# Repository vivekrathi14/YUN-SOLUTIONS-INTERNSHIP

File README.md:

# SMART MANAGEMENT OF BINS

**Project Name** - Smart Management of Bins

**Area** - Embedded Systems, IoT

**Technolgies** - In Application Programming (IAP), Watchdog Timer (WDT), Flash Over Through Air (FOTA), GSM-2G Communication, GNSS, TCP, HTTP, FTP, I2C, Concurrency, UART, Serial Communication, Antenna Chip Design, GPIOs, ARM Cortex M0, M0516LDN, Arduino Nano

**Hardware** - ARM Cortex M0 M0516LDN

**Programming** - Embedded C

**Description** -

1. Measured the environmental quatities using sensors (Ultrasonic, IR, keypad, GSM) user input.
2. Abstracted the the senor data and sent it to server (cloud) for data handling and analysis.
3. Created to keep track of goods/objects loaded and unloaded form dockyard (or any environmental settings). 
4. Deployed for the client to keep track of packed and unpacked medicince pouches/bags in his inventory.
5. Use advanced features lik In Application Programming & Flash Over Throught Air to boot the device with updated new firmware remotely.

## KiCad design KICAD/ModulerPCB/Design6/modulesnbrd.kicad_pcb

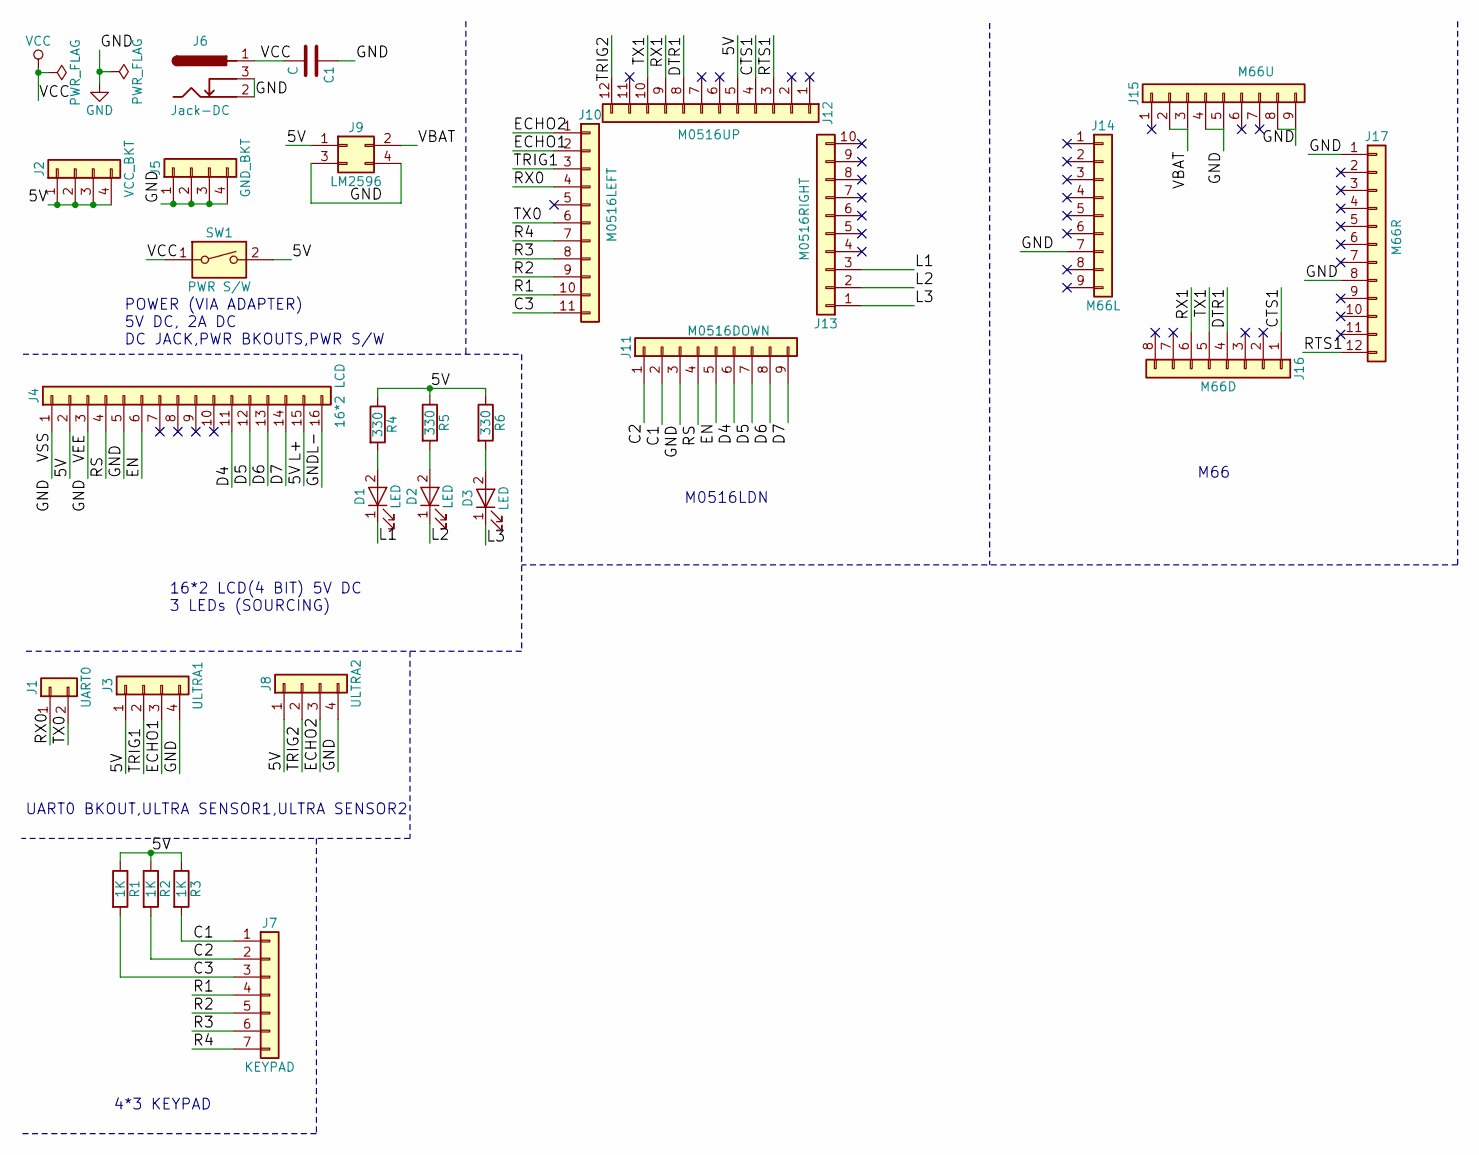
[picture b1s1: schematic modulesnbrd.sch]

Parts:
C1: C; C_Disc_D3.4mm_W2.1mm_P2.50mm
D1, D2, D3: LED; LED_D5.0mm
J1: UART0; Pin_Header_Straight_1x02_Pitch2.54mm
J2: VCC_BKT; Pin_Header_Straight_1x04_Pitch2.54mm
J3: ULTRA1; Pin_Header_Straight_1x04_Pitch2.54mm
J4: 16*2 LCD; Pin_Header_Straight_1x16_Pitch2.54mm
J5: GND_BKT; Pin_Header_Straight_1x04_Pitch2.54mm
J6: Jack-DC; Barrel_Jack_CUI_PJ-102AH
J7: KEYPAD; Pin_Header_Straight_1x07_Pitch2.54mm
J8: ULTRA2; Pin_Header_Straight_1x04_Pitch2.54mm
J9: LM2596
J10: M0516LEFT; Pin_Header_Straight_1x11_Pitch2.54mm
J11: M0516DOWN; Pin_Header_Straight_1x09_Pitch2.54mm
J12: M0516UP; Pin_Header_Straight_1x12_Pitch2.54mm
J13: M0516RIGHT; Pin_Header_Straight_1x10_Pitch2.54mm
J14: M66L; Pin_Header_Straight_1x09_Pitch2.54mm
J15: M66U; Pin_Header_Straight_1x09_Pitch2.54mm
J16: M66D; Pin_Header_Straight_1x08_Pitch2.54mm
J17: M66R; Pin_Header_Straight_1x12_Pitch2.54mm
R1, R2, R3: 1K; R_Axial_DIN0204_L3.6mm_D1.6mm_P5.08mm_Horizontal
R4, R5, R6: 330; R_Axial_DIN0204_L3.6mm_D1.6mm_P5.08mm_Horizontal
SW1: PWR S/W; SW_DIP_x1_W7.62mm_Slide

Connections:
/5V: J2.1, J2.2, J2.3, J2.4, J3.1, J4.2, J4.15, J8.1, J9.1, J12.5, R1.1, R2.1, R3.1, R4.1, R5.1, R6.1, SW1.2
/C1: J7.1, J11.2, R3.2
/C2: J7.2, J11.1, R2.2
/C3: J7.3, J10.11, R1.2
/CTS1: J12.4, J16.1
/D4: J4.11, J11.6
/D5: J4.12, J11.7
/D6: J4.13, J11.8
/D7: J4.14, J11.9
/DTR1: J12.8, J16.4
/ECHO1: J3.3, J10.2
/ECHO2: J8.3, J10.1
/EN: J4.6, J11.5
/L1: D1.1 (K), J13.3
/L2: D2.1 (K), J13.2
/L3: D3.1 (K), J13.1
/R1: J7.4, J10.10
/R2: J7.5, J10.9
/R3: J7.6, J10.8
/R4: J7.7, J10.7
/RS: J4.4, J11.4
/RTS1: J12.3, J17.12
/RX0: J1.1, J10.4
/RX1: J12.9, J16.6
/TRIG1: J3.2, J10.3
/TRIG2: J8.2, J12.12
/TX0: J1.2, J10.6
/TX1: J12.10, J16.5
/VBAT: J9.2, J15.2, J15.3
GND: C1.1, J3.4, J4.1, J4.3, J4.5, J4.16, J5.1, J5.2, J5.3, J5.4, J6.2, J6.3, J8.4, J9.3, J9.4, J11.3, J14.7, J15.4, J15.5, J15.8, J15.9, J17.1, J17.8
unnamed: D1.2 (A), R4.2
unnamed: D2.2 (A), R5.2
unnamed: D3.2 (A), R6.2
VCC: C1.2, J6.1, SW1.1

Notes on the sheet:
POWER (VIA ADAPTER) 5V DC, 2A DC DC JACK,PWR BKOUTS,PWR S/W
16*2 LCD(4 BIT) 5V DC 3 LEDs (SOURCING)
UART0 BKOUT,ULTRA SENSOR1,ULTRA SENSOR2
4*3 KEYPAD
M0516LDN
M66

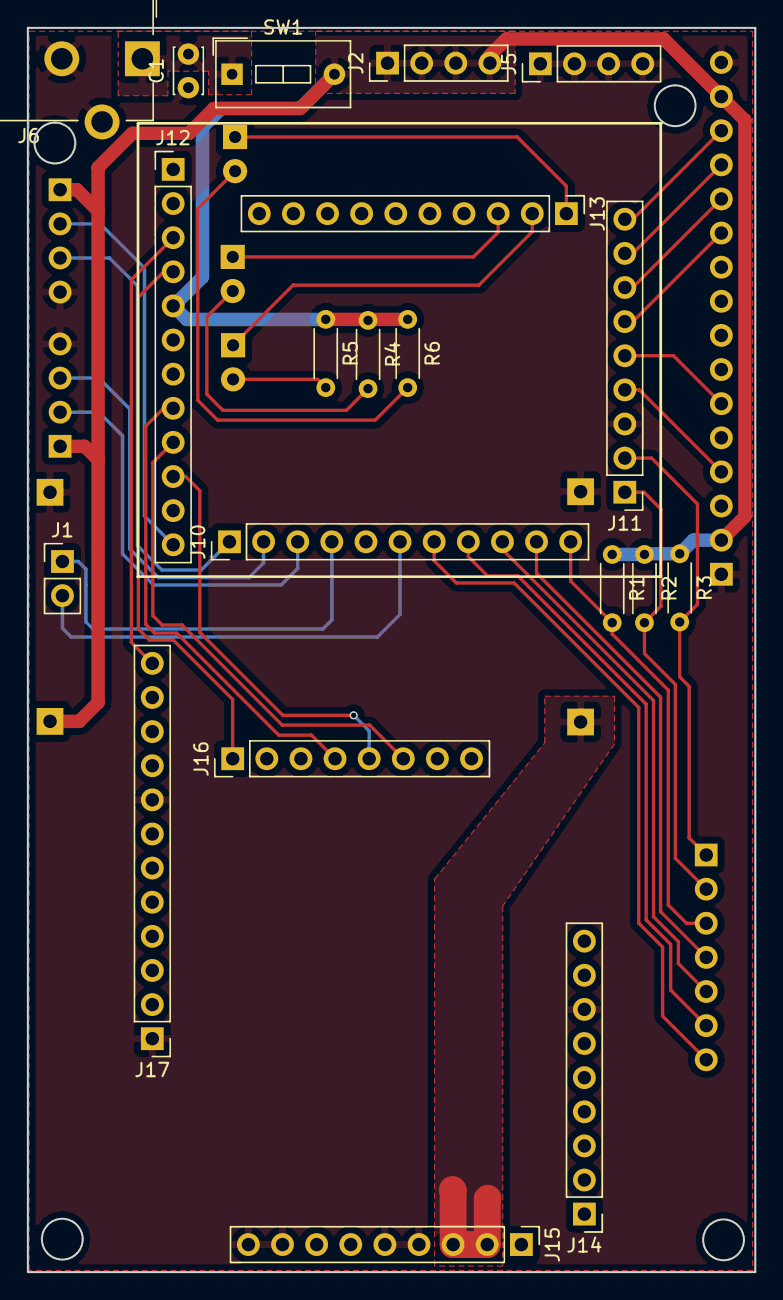
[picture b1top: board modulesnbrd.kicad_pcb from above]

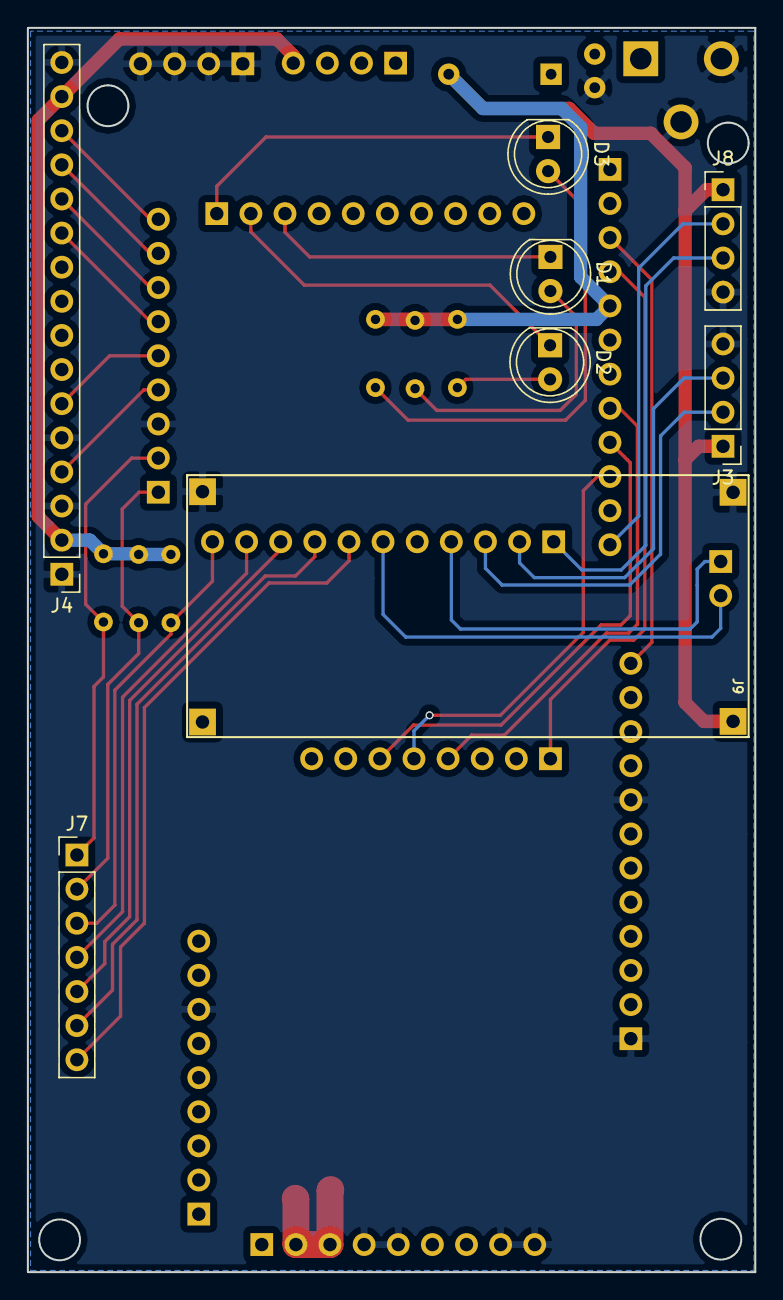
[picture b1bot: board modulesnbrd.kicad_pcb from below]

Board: 2 copper layers, 54.1 x 92.6 mm, 28 parts (8 on the bottom side), 34 nets.

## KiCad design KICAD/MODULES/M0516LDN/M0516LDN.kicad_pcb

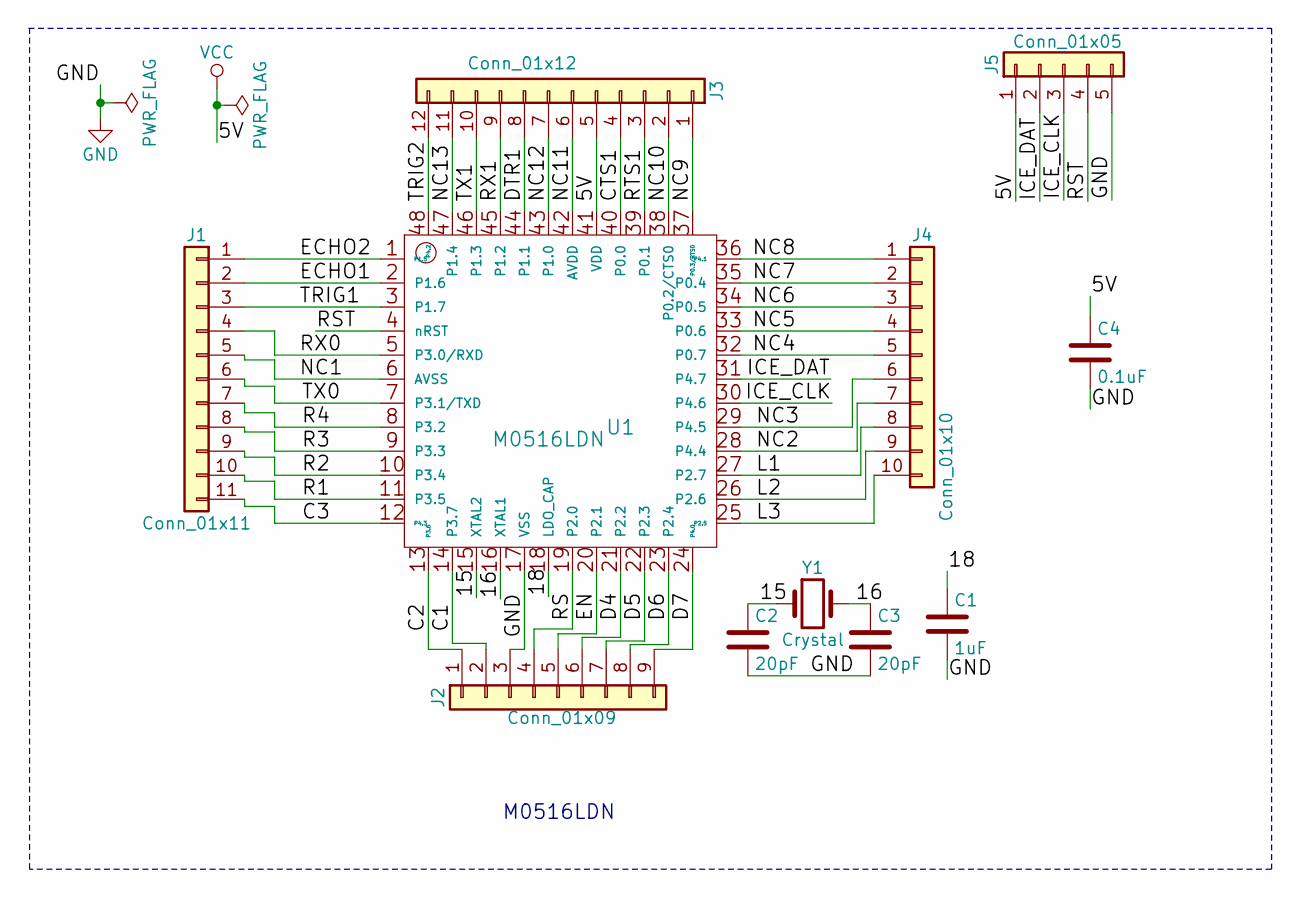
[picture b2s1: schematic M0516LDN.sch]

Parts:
C1: 1uF; C_0603_HandSoldering
C2, C3: 20pF; C_0603_HandSoldering
C4: 0.1uF; C_0603_HandSoldering
J1: Conn_01x11; Pin_Header_Straight_1x11_Pitch2.54mm
J2: Conn_01x09; Pin_Header_Straight_1x09_Pitch2.54mm
J3: Conn_01x12; Pin_Header_Straight_1x12_Pitch2.54mm
J4: Conn_01x10; Pin_Header_Straight_1x10_Pitch2.54mm
J5: Conn_01x05; Pin_Header_Straight_1x05_Pitch2.54mm
U1: M0516LDN; LQFP-48_7x7mm_Pitch0.5mm
Y1: Crystal; Crystal_HC50_Vertical

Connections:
/15: C2.1, U1.15 (XTAL2), Y1.1
/16: C3.1, U1.16 (XTAL1), Y1.2
/18: C1.1, U1.18 (LDO_CAP)
/C1: J2.2, U1.14 (P3.7)
/C2: J2.1, U1.13 (P3.6)
/C3: J1.11, U1.12 (P4.3)
/CTS1: J3.4, U1.40 (P0.0)
/D4: J2.6, U1.21 (P2.2)
/D5: J2.7, U1.22 (P2.3)
/D6: J2.8, U1.23 (P2.4)
/D7: J2.9, U1.24 (P4.0)
/DTR1: J3.8, U1.44 (P1.1)
/ECHO1: J1.2, U1.2 (P1.6)
/ECHO2: J1.1, U1.1 (P1.5)
/EN: J2.5, U1.20 (P2.1)
/ICE_CLK: J5.3, U1.30 (P4.6)
/ICE_DAT: J5.2, U1.31 (P4.7)
/L1: J4.8, U1.27 (P2.7)
/L2: J4.9, U1.26 (P2.6)
/L3: J4.10, U1.25 (P2.5)
/NC1: J1.5, U1.6 (AVSS)
/NC2: J4.7, U1.28 (P4.4)
/NC3: J4.6, U1.29 (P4.5)
/NC4: J4.5, U1.32 (P0.7)
/NC5: J4.4, U1.33 (P0.6)
/NC6: J4.3, U1.34 (P0.5)
/NC7: J4.2, U1.35 (P0.4)
/NC8: J4.1, U1.36 (P4.1)
/NC9: J3.1, U1.37 (P0.3/RTS0)
/NC10: J3.2, U1.38 (P0.2/CTS0)
/NC11: J3.6, U1.42 (AVDD)
/NC12: J3.7, U1.43 (P1.0)
/NC13: J3.11, U1.47 (P1.4)
/R1: J1.10, U1.11 (P3.5)
/R2: J1.9, U1.10 (P3.4)
/R3: J1.8, U1.9 (P3.3)
/R4: J1.7, U1.8 (P3.2)
/RS: J2.4, U1.19 (P2.0)
/RST: J5.4, U1.4 (nRST)
/RTS1: J3.3, U1.39 (P0.1)
/RX0: J1.4, U1.5 (P3.0/RXD)
/RX1: J3.9, U1.45 (P1.2)
/TRIG1: J1.3, U1.3 (P1.7)
/TRIG2: J3.12, U1.48 (P4.2)
/TX0: J1.6, U1.7 (P3.1/TXD)
/TX1: J3.10, U1.46 (P1.3)
GND: C1.2, C2.2, C3.2, C4.2, J2.3, J5.5, U1.17 (VSS)
VCC: C4.1, J3.5, J5.1, U1.41 (VDD)

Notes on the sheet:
M0516LDN

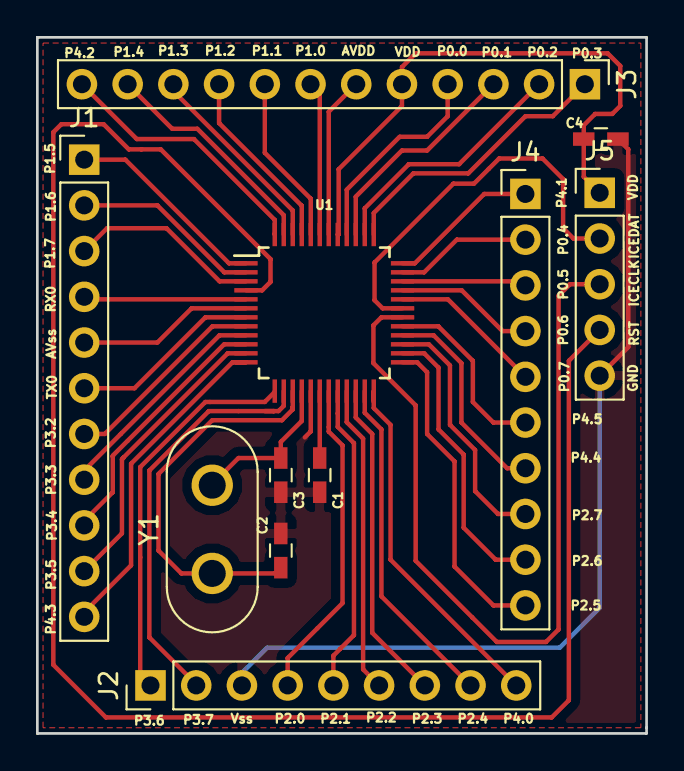
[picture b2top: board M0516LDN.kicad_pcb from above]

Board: 2 copper layers, 33.8 x 38.7 mm, 11 parts (0 on the bottom side), 48 nets.

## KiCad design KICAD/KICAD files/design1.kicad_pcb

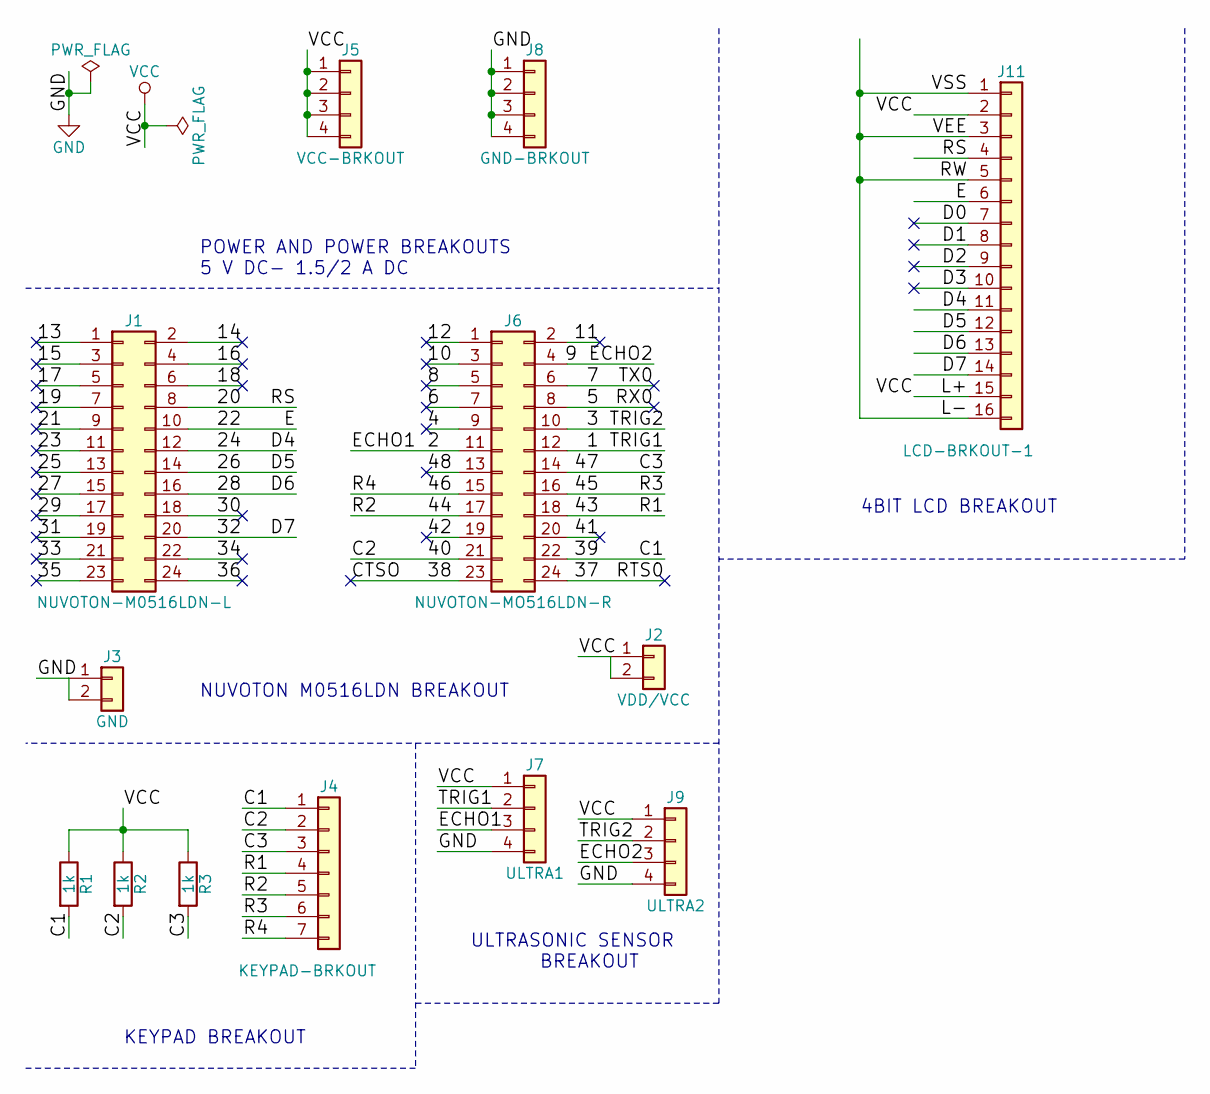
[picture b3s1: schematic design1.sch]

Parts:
J1: NUVOTON-M0516LDN-L; Socket_Strip_Straight_2x12_Pitch2.54mm
J2: VDD/VCC; Socket_Strip_Straight_1x02_Pitch2.54mm
J3: GND; Socket_Strip_Straight_1x02_Pitch2.54mm
J4: KEYPAD-BRKOUT; Pin_Header_Straight_1x07_Pitch2.54mm
J5: VCC-BRKOUT; Pin_Header_Straight_1x04_Pitch2.54mm
J6: NUVOTON-MO516LDN-R; Socket_Strip_Straight_2x12_Pitch2.54mm
J7: ULTRA1; Pin_Header_Straight_1x04_Pitch2.54mm
J8: GND-BRKOUT; Pin_Header_Straight_1x04_Pitch2.54mm
J9: ULTRA2; Pin_Header_Straight_1x04_Pitch2.54mm
J11: LCD-BRKOUT-1; Pin_Header_Straight_1x16_Pitch2.54mm
R1, R2, R3: 1k; R_Axial_DIN0204_L3.6mm_D1.6mm_P2.54mm_Vertical

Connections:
/1: J6.12, J7.2
/2: J6.11, J7.3
/3: J6.10, J9.2
/4: J6.9
/5: J6.8
/6: J6.7
/7: J6.6
/8: J6.5
/9: J6.4, J9.3
/10: J6.3
/11: J6.2
/12: J6.1
/13: J1.1
/14: J1.2
/15: J1.3
/16: J1.4
/17: J1.5
/18: J1.6
/19: J1.7
/20: J1.8, J11.4
/21: J1.9
/22: J1.10, J11.6
/23: J1.11
/24: J1.12, J11.11
/25: J1.13
/26: J1.14, J11.12
/27: J1.15
/28: J1.16, J11.13
/29: J1.17
/30: J1.18
/31: J1.19
/32: J1.20, J11.14
/33: J1.21
/34: J1.22
/35: J1.23
/36: J1.24
/37: J6.24
/38: J6.23
/39: J4.1, J6.22, R1.2
/40: J4.2, J6.21, R2.2
/41: J6.20
/42: J6.19
/43: J4.4, J6.18
/44: J4.5, J6.17
/45: J4.6, J6.16
/46: J4.7, J6.15
/47: J4.3, J6.14, R3.2
/48: J6.13
/D0: J11.7
/D1: J11.8
/D2: J11.9
/D3: J11.10
/L-: J11.1, J11.3, J11.5, J11.16
GND: J3.1, J3.2, J7.4, J8.1, J8.2, J8.3, J8.4, J9.4
VCC: J2.1, J2.2, J5.1, J5.2, J5.3, J5.4, J7.1, J9.1, J11.2, J11.15, R1.1, R2.1, R3.1

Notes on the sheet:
POWER AND POWER BREAKOUTS 5 V DC- 1.5/2 A DC
NUVOTON M0516LDN BREAKOUT
KEYPAD BREAKOUT
ULTRASONIC SENSOR BREAKOUT
4BIT LCD BREAKOUT

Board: 2 copper layers, 13 parts (0 on the bottom side), 20 nets, no tracks yet.

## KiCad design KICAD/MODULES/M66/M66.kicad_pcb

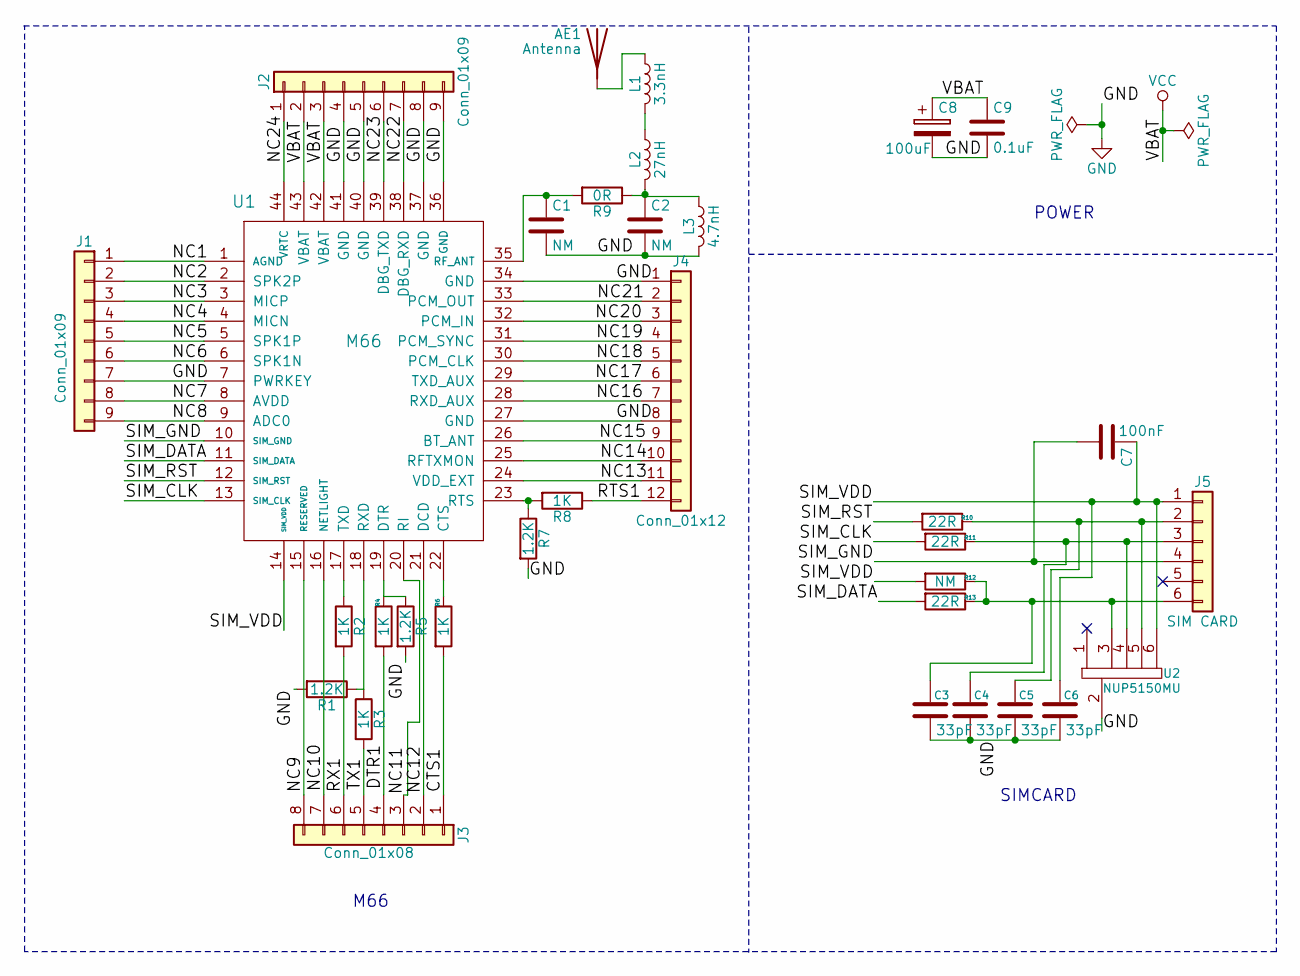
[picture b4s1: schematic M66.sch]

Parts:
AE1: Antenna; W3070
C1, C2: NM; C_0603_HandSoldering
C3, C4, C5, C6: 33pF; C_0603_HandSoldering
C7: 100nF; C_0603_HandSoldering
C8: 100uF; C_1210_HandSoldering
C9: 0.1uF; C_0603_HandSoldering
J1, J2: Conn_01x09; Pin_Header_Straight_1x09_Pitch2.54mm
J3: Conn_01x08; Pin_Header_Straight_1x08_Pitch2.54mm
J4: Conn_01x12; Pin_Header_Straight_1x12_Pitch2.54mm
J5: SIM CARD; SIMCARDHOLDER
L1: 3.3nH; L_0603_HandSoldering
L2: 27nH; L_0603_HandSoldering
L3: 4.7nH; L_0603_HandSoldering
R1, R5, R7: 1.2K; R_0603_HandSoldering
R2, R3, R4, R6, R8: 1K; R_0603_HandSoldering
R9: 0R; R_0603_HandSoldering
R10, R11, R13: 22R; R_0603_HandSoldering
R12: NM; R_0603_HandSoldering
U1: M66; M66_modified
U2: NUP5150MU; SOT-23-6_Handsoldering

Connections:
/CTS1: J3.1, R6.2
/DTR1: J3.4, R4.2
/NC1: J1.1, U1.1 (AGND)
/NC2: J1.2, U1.2 (SPK2P)
/NC3: J1.3, U1.3 (MICP)
/NC4: J1.4, U1.4 (MICN)
/NC5: J1.5, U1.5 (SPK1P)
/NC6: J1.6, U1.6 (SPK1N)
/NC7: J1.8, U1.8 (AVDD)
/NC8: J1.9, U1.9 (ADC0)
/NC9: J3.8, U1.15 (RESERVED)
/NC10: J3.7, U1.16 (NETLIGHT)
/NC11: J3.3, U1.20 (RI)
/NC12: J3.2, U1.21 (DCD)
/NC13: J4.11, U1.24 (VDD_EXT)
/NC14: J4.10, U1.25 (RFTXMON)
/NC15: J4.9, U1.26 (BT_ANT)
/NC16: J4.7, U1.28 (RXD_AUX)
/NC17: J4.6, U1.29 (TXD_AUX)
/NC18: J4.5, U1.30 (PCM_CLK)
/NC19: J4.4, U1.31 (PCM_SYNC)
/NC20: J4.3, U1.32 (PCM_IN)
/NC21: J4.2, U1.33 (PCM_OUT)
/NC22: J2.7, U1.38 (DBG_RXD)
/NC23: J2.6, U1.39 (DBG_TXD)
/NC24: J2.1, U1.44 (VRTC)
/RTS1: J4.12, R8.1
/RX1: J3.6, R2.2
/SIM_CLK: R11.2, U1.13 (SIM_CLK)
/SIM_DATA: R13.2, U1.11 (SIM_DATA)
/SIM_GND: C7.2, J5.4, U1.10 (SIM_GND)
/SIM_RST: R10.2, U1.12 (SIM_RST)
/SIM_VDD: C6.1, C7.1, J5.1, R12.2, U1.14 (SIM_VDD), U2.6
/TX1: J3.5, R3.2
GND: C1.2, C2.2, C3.2, C4.2, C5.2, C6.2, C8.2, C9.2, J1.7, J2.4, J2.5, J2.8, J2.9, J4.1, J4.8, L3.2, R1.2, R5.2, R7.2, U1.7 (PWRKEY), U1.27 (GND), U1.34 (GND), U1.36 (GND), U1.37 (GND), U1.40 (GND), U1.41 (GND), U2.2
unnamed: AE1.1, L1.1
unnamed: C1.1, R9.2, U1.35 (RF_ANT)
unnamed: C2.1, L2.2, L3.1, R9.1
unnamed: C3.1, J5.6, R12.1, R13.1, U2.3
unnamed: C4.1, J5.3, R11.1, U2.4
unnamed: C5.1, J5.2, R10.1, U2.5
unnamed: L1.2, L2.1
unnamed: R1.1, R3.1, U1.18 (RXD)
unnamed: R2.1, U1.17 (TXD)
unnamed: R4.1, R5.1, U1.19 (DTR)
unnamed: R6.1, U1.22 (CTS)
unnamed: R7.1, R8.2, U1.23 (RTS)
VCC: C8.1, C9.1, J2.2, J2.3, U1.42 (VBAT), U1.43 (VBAT)

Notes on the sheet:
POWER
SIMCARD
M66

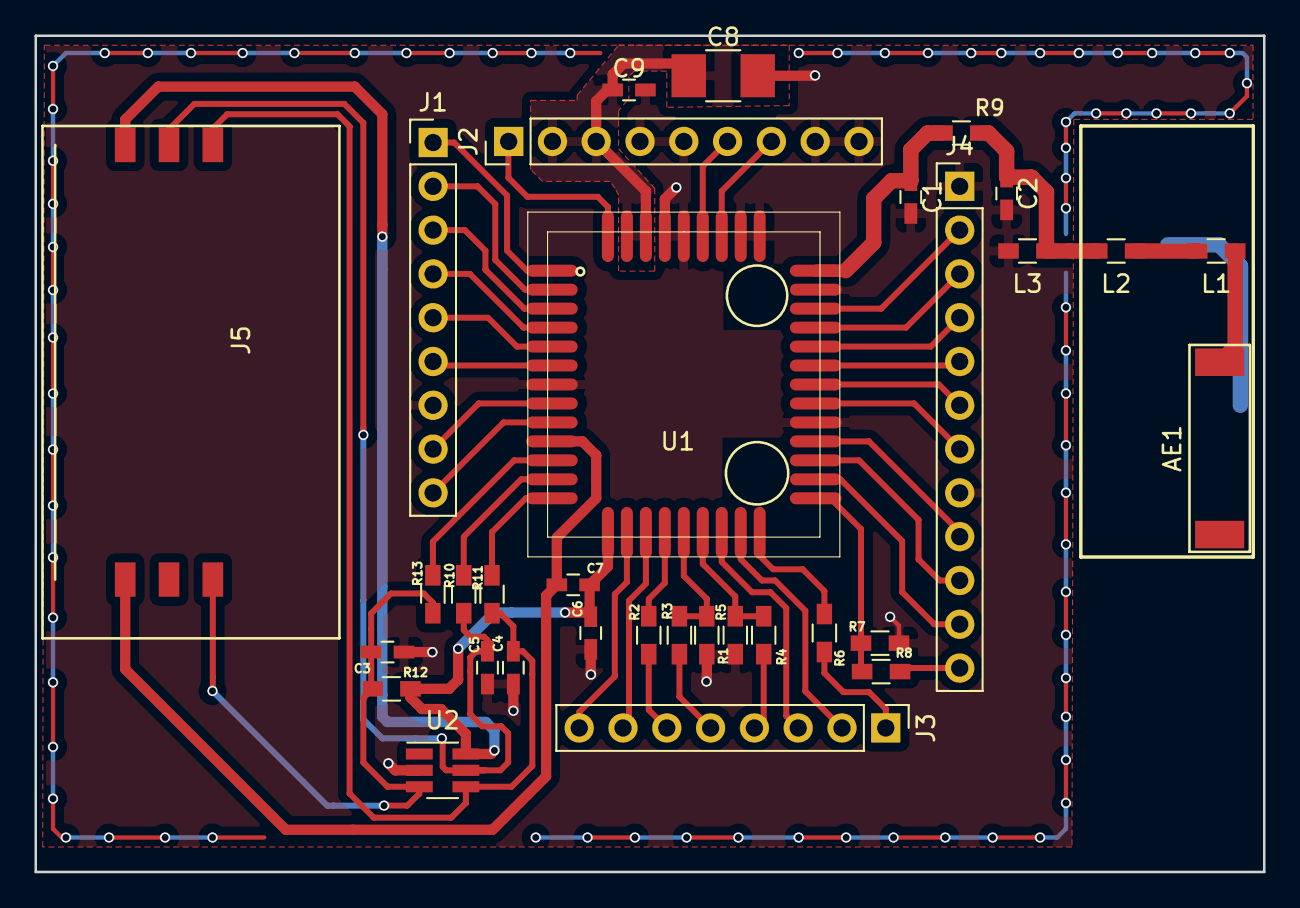
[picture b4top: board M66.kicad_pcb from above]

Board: 2 copper layers, 71.2 x 48.5 mm, 33 parts (0 on the bottom side), 48 nets.

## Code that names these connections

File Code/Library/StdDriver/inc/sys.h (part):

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
#define SYS_MFP_P00_GPIO        0x00000000UL /*!< P0_MFP pin 0 setting for GPIO */
#define SYS_MFP_P00_AD0         0x00000001UL /*!< P0_MFP pin 0 setting for AD0  */
#define SYS_MFP_P00_CTS1        0x00000100UL /*!< P0_MFP pin 0 setting for CTS1 */
#define SYS_MFP_P00_TXD1        0x00000101UL /*!< P0_MFP pin 0 setting for TXD1 */
#define SYS_MFP_P00_ACMP3_P     0x01000000UL /*!< P0_MFP pin 0 setting for ACMP3_P */
#define SYS_MFP_P00_Msk         0x01000101UL /*!< P0_MFP pin 0 mask             */

#define SYS_MFP_P01_GPIO        0x00000000UL /*!< P0_MFP pin 1 setting for GPIO */
#define SYS_MFP_P01_AD1         0x00000002UL /*!< P0_MFP pin 1 setting for AD1  */
#define SYS_MFP_P01_RTS1        0x00000200UL /*!< P0_MFP pin 1 setting for RTS1 */
#define SYS_MFP_P01_RXD1        0x00000202UL /*!< P0_MFP pin 1 setting for RXD1 */
#define SYS_MFP_P01_ACMP3_N     0x02000000UL /*!< P0_MFP pin 1 setting for ACMP3_N */
#define SYS_MFP_P01_Msk         0x02000202UL /*!< P0_MFP pin 1 mask             */
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#define SYS_MFP_P45_Msk     0x00002020UL /*!< P4_MFP pin 5 mask             */

#define SYS_MFP_P46_GPIO    0x00000000UL /*!< P4_MFP pin 6 setting for GPIO    */
#define SYS_MFP_P46_ICE_CLK 0x00000040UL /*!< P4_MFP pin 6 setting for ICE_CLK */
#define SYS_MFP_P46_Msk     0x00004040UL /*!< P4_MFP pin 6 mask                */

#define SYS_MFP_P47_GPIO    0x00000000UL /*!< P4_MFP pin 7 setting for GPIO    */
#define SYS_MFP_P47_ICE_DAT 0x00000080UL /*!< P4_MFP pin 7 setting for ICE_DAT */
#define SYS_MFP_P47_Msk     0x00008080UL /*!< P4_MFP pin 7 mask                */


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
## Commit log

2020-01-02 Harware & Software Development Prototype Phase
2020-01-02 Deleted
2020-01-02 Rename Readme.txt to README.md

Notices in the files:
Code/Library/StdDriver/inc/sys.h:
Copyright (C) 2011 Nuvoton Technology Corp. All rights reserved.
